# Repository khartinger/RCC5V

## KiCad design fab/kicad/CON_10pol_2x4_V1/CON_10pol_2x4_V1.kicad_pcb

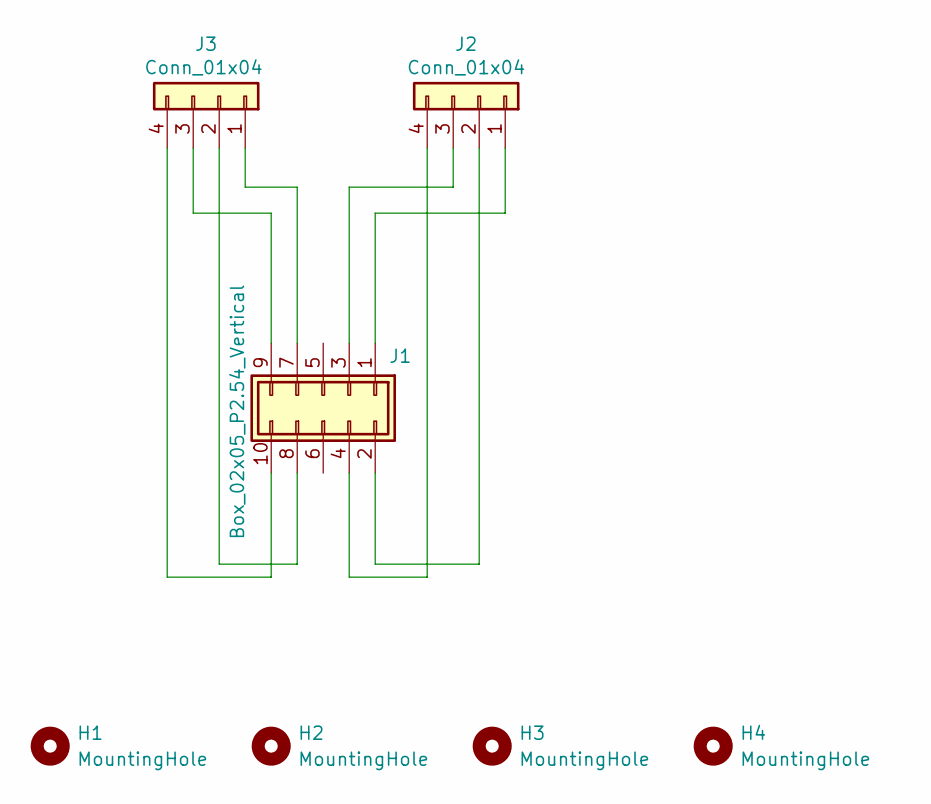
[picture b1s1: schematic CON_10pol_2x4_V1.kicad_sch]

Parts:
H1, H2, H3, H4: MountingHole; MountingHole_2.2mm_M2_Pad_TopBottom_kh
J1: Box_02x05_P2.54_Vertical; Box_02x05_P2.54mm_Vertical_kh
J2, J3: Conn_01x04; PinSocket_1x04_P2.54mm_Vertical_kh

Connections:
/0V: J1.5
/V_I2C: J1.6
unnamed: J1.1, J2.1
unnamed: J1.2, J2.2
unnamed: J1.3, J2.3
unnamed: J1.4, J2.4
unnamed: J1.7, J3.1
unnamed: J1.8, J3.2
unnamed: J1.9, J3.3
unnamed: J1.10, J3.4

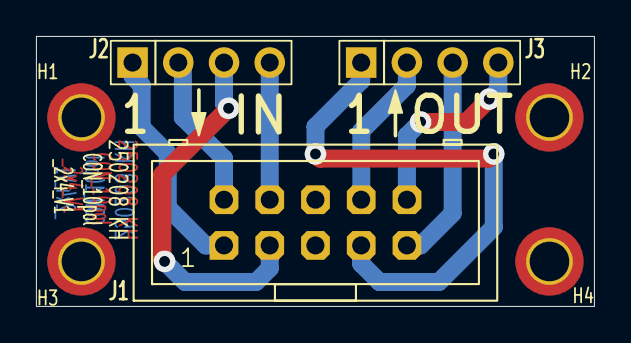
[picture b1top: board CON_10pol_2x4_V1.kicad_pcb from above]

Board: 2 copper layers, 31.0 x 15.0 mm, 7 parts (0 on the bottom side), 8 nets.

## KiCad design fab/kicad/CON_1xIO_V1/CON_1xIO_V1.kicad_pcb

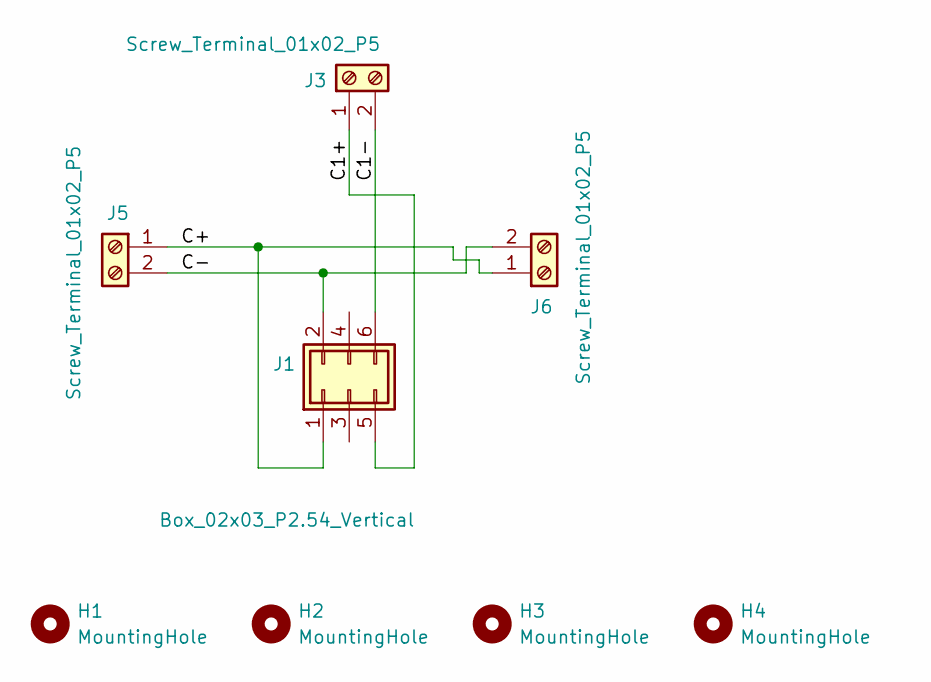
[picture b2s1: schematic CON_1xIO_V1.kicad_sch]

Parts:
H1, H2, H3, H4: MountingHole; MountingHole_2.2mm_M2_Pad_TopBottom_kh
J1: Box_02x03_P2.54_Vertical; Box_02x03_P2.54mm_Vertical_kh
J3, J5, J6: Screw_Terminal_01x02_P5

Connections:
/C1+: J1.5, J3.1
/C1-: J1.6, J3.2
/C+: J1.1, J5.1, J6.1
/C-: J1.2, J5.2, J6.2

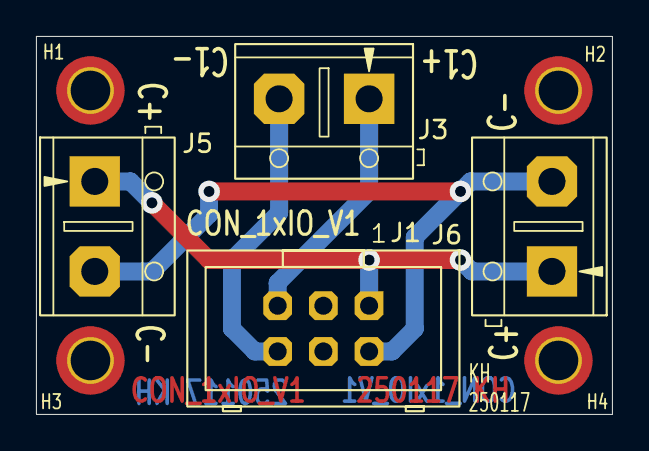
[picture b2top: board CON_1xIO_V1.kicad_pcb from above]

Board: 2 copper layers, 32.0 x 21.0 mm, 8 parts (0 on the bottom side), 4 nets.

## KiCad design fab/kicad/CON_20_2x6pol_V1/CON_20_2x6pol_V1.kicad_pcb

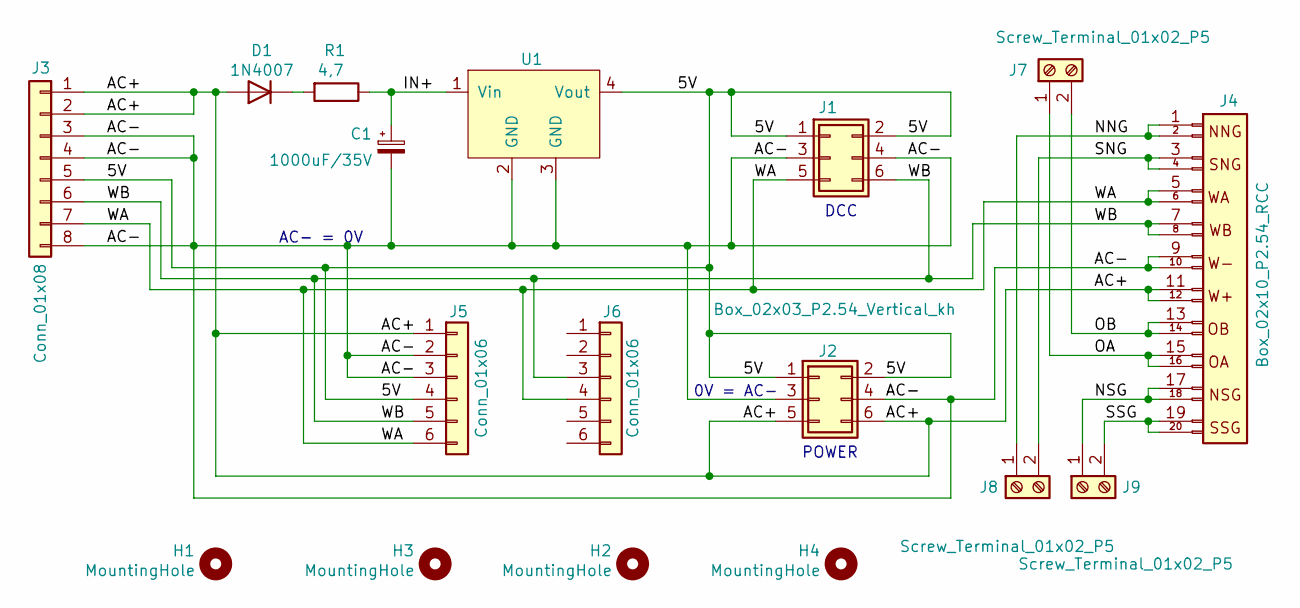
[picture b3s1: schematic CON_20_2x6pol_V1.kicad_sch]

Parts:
C1: 1000uF/35V; CP_Radial_L20.0mm_D10.0mm_P5.08mm_Horizontal
D1: 1N4007; D_DO-41_SOD81_P3.81mm_Vertical_AnodeUp_kh
H1, H2, H3, H4: MountingHole; MountingHole_2.7mm_M2.5_DIN965_Pad_TopBottom
J1: Box_02x03_P2.54_Vertical; Box_02x03_P2.54mm_Vertical_kh
J2: Box_02x03_P2.54_Vertical_kh; Box_02x03_P2.54mm_Vertical_kh
J3: Conn_01x08; PinSocket_1x08_P2.54mm_Vertical_kh
J4: Box_02x10_P2.54_RCC; Box_02x10_P2.54mm_Vertical_kh
J5, J6: Conn_01x06; PinSocket_1x06_P2.54mm_Vertical_kh
J7, J8, J9: Screw_Terminal_01x02_P5
R1: 4,7; R_Axial_Power_L25.0mm_W6.4mm_P27.94mm_kh
U1: DCDC_StepDown_LM2596; DCDC_StepDown_LM2596_PinsOnly

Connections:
/5V: J1.1, J1.2, J2.1, J2.2, J3.5, J5.4, U1.4 (Vout)
/AC+: D1.2 (A), J2.5, J2.6, J3.1, J3.2, J4.11, J4.12, J5.1
/AC-: C1.2, J1.3, J1.4, J2.3, J2.4, J3.3, J3.4, J3.8, J4.9, J4.10, J5.2, J5.3, U1.2 (GND), U1.3 (GND)
/IN+: C1.1, R1.1, U1.1 (Vin)
/NNG: J4.1, J4.2, J8.1
/NSG: J4.17, J4.18, J9.1
/OA: J4.15, J4.16, J7.1
/OB: J4.13, J4.14, J7.2
/SNG: J4.3, J4.4, J8.2
/SSG: J4.19, J4.20, J9.2
/WA: J1.5, J3.7, J4.5, J4.6, J5.6, J6.4
/WB: J1.6, J3.6, J4.7, J4.8, J5.5, J6.3
unnamed: D1.1 (K), R1.2

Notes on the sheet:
AC- = 0V
POWER
0V = AC-
DCC

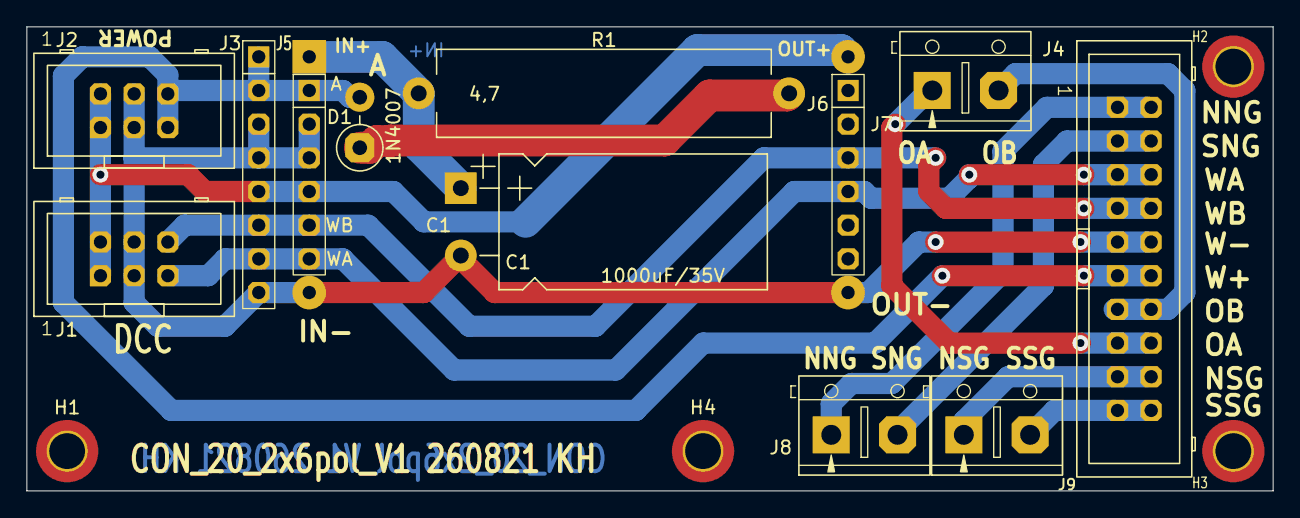
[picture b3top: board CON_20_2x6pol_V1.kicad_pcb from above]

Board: 2 copper layers, 94.0 x 35.0 mm, 17 parts (0 on the bottom side), 13 nets.

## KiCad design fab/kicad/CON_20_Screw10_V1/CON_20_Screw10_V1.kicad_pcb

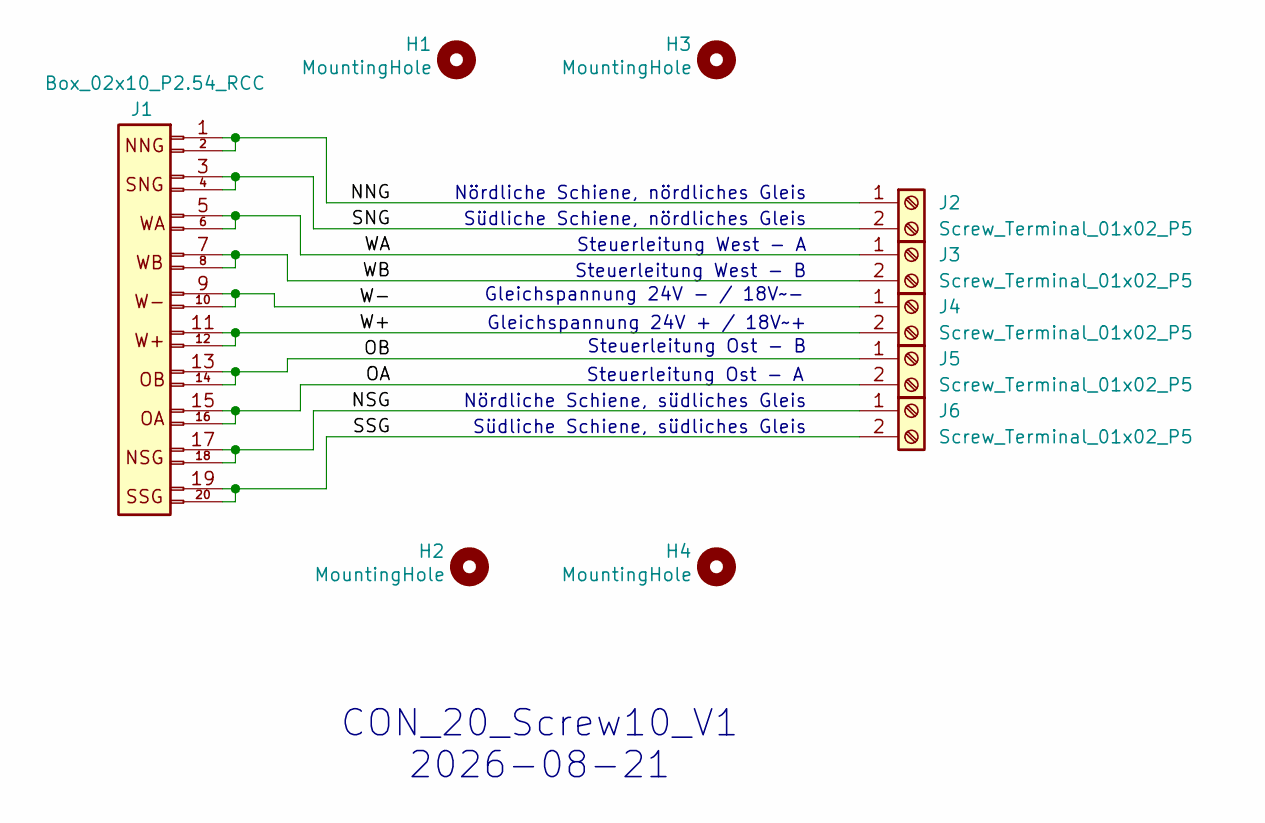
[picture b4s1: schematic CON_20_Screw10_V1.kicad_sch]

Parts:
H1, H2, H3, H4: MountingHole; MountingHole_2.7mm_M2.5_DIN965_Pad_TopBottom
J1: Box_02x10_P2.54_RCC; Box_02x10_P2.54mm_Vertical_kh
J2, J3, J4, J5, J6: Screw_Terminal_01x02_P5

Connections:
/NNG: J1.1, J1.2, J2.1
/NSG: J1.17, J1.18, J6.1
/OA: J1.15, J1.16, J5.2
/OB: J1.13, J1.14, J5.1
/SNG: J1.3, J1.4, J2.2
/SSG: J1.19, J1.20, J6.2
/W+: J1.11, J1.12, J4.2
/W-: J1.9, J1.10, J4.1
/WA: J1.5, J1.6, J3.1
/WB: J1.7, J1.8, J3.2

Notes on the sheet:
CON_20_Screw10_V1 2026-08-21
Südliche Schiene, südliches Gleis
Südliche Schiene, nördliches Gleis
Gleichspannung 24V - / 18V~-
Nördliche Schiene, nördliches Gleis
Steuerleitung West - A
Steuerleitung Ost - B
Steuerleitung West - B
Gleichspannung 24V + / 18V~+
Nördliche Schiene, südliches Gleis
Steuerleitung Ost - A

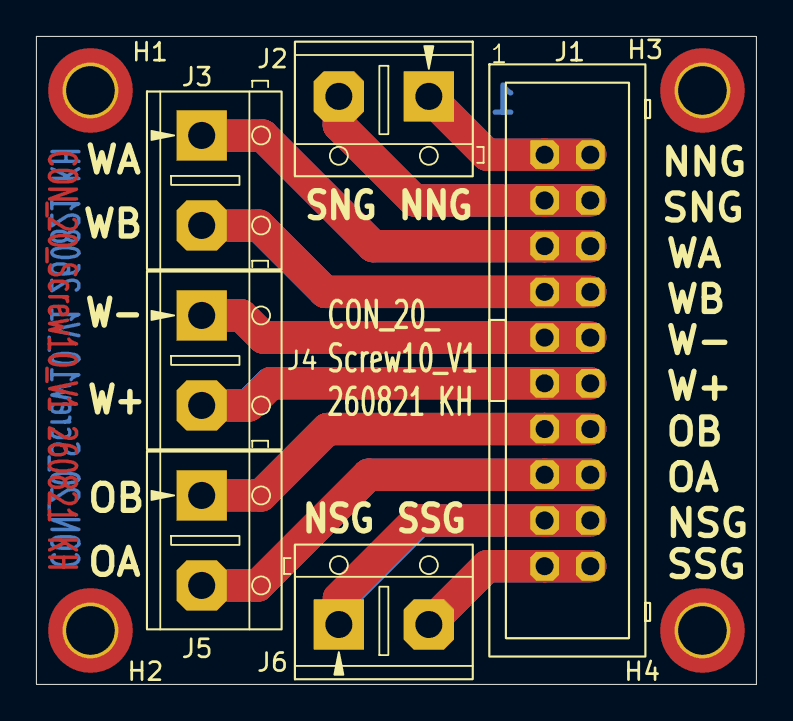
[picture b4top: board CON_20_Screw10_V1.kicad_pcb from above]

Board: 2 copper layers, 40.0 x 36.0 mm, 10 parts (0 on the bottom side), 10 nets.
